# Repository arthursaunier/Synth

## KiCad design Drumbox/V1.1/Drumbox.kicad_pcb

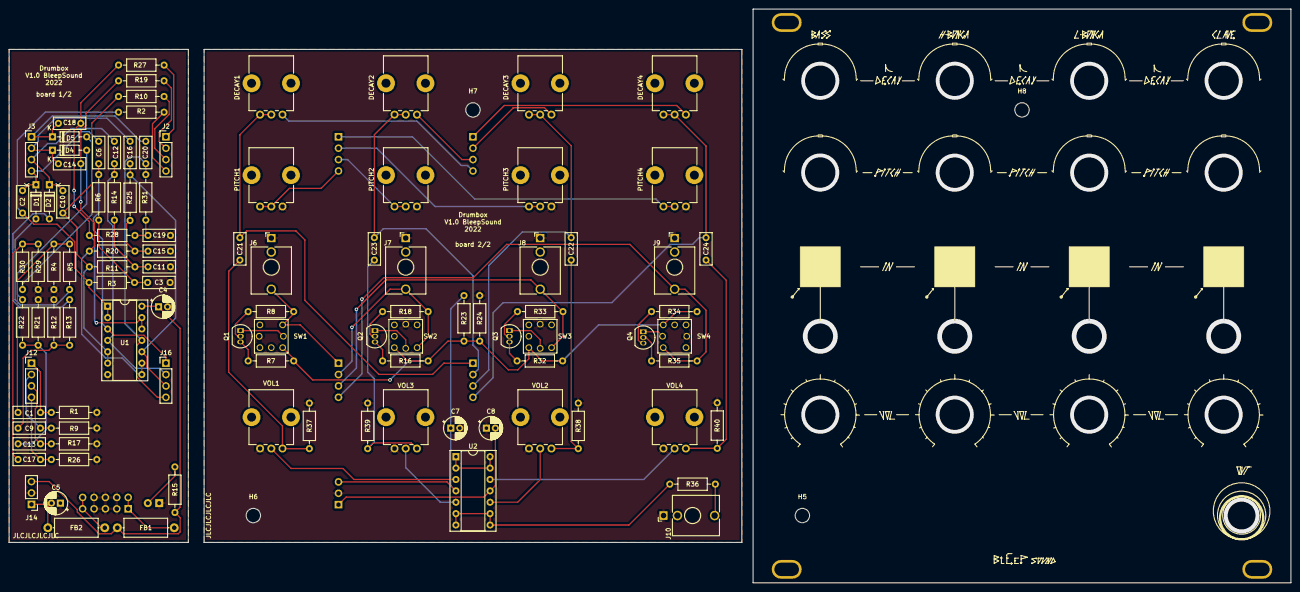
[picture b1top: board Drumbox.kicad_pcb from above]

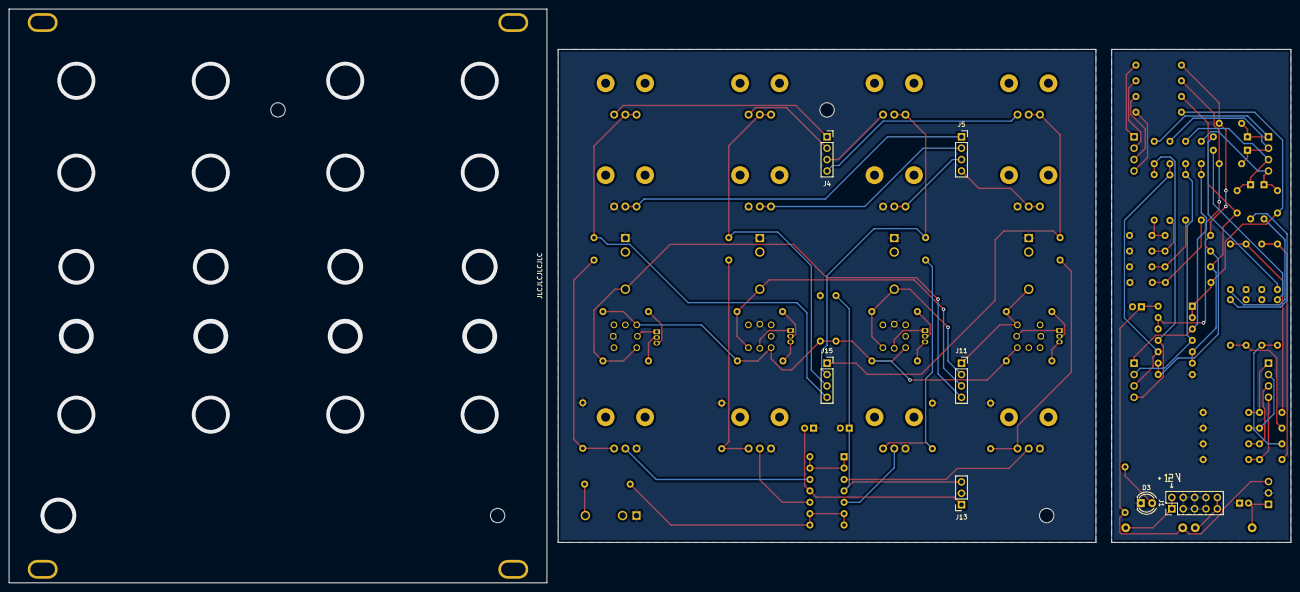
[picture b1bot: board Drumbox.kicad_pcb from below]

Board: 2 copper layers, 286.0 x 128.0 mm, 117 parts (7 on the bottom side), 61 nets.

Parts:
C1, C3: 150nF; C_Disc_D7.0mm_W2.5mm_P5.00mm
C2, C6: 47nF; C_Disc_D7.0mm_W2.5mm_P5.00mm
C4, C5: 10µ; CP_Radial_D5.0mm_P2.00mm
C7, C8: 100n; CP_Radial_D5.0mm_P2.00mm
C9, C11: 33nF; C_Disc_D7.0mm_W2.5mm_P5.00mm
C10, C12: 10nF; C_Disc_D7.0mm_W2.5mm_P5.00mm
C13, C15: 39nF; C_Disc_D7.0mm_W2.5mm_P5.00mm
C14, C16: 12nF; C_Disc_D7.0mm_W2.5mm_P5.00mm
C17: 4.7nF; C_Disc_D7.0mm_W2.5mm_P5.00mm
C18, C20: 1.5nF; C_Disc_D7.0mm_W2.5mm_P5.00mm
C19: 56nF; C_Disc_D7.0mm_W2.5mm_P5.00mm
C21, C22, C23, C24: .1µF; C_Disc_D7.0mm_W2.5mm_P5.00mm
D1, D2, D4, D5: 1N4148; D_DO-35_SOD27_P7.62mm_Horizontal
D3: LED-12V; LED_D4.0mm
DECAY1, DECAY2, DECAY3, DECAY4: 470k; Potentiometer_Bourns_PTV09A-1_Single_Vertical
FB1, FB2: 10R; L_Axial_L9.5mm_D4.0mm_P12.70mm_Horizontal_Fastron_SMCC
H1, H2, H3, H4: MountingHole; Doepfer Mounting hole
H5, H6, H7, H8: SpacerHoles; MountingHole_3.2mm_M3
J1: Power Input; PinHeader_2x05_P2.54mm_Vertical
J2, J3, J12, J16: Conn_01x04_Male; PinHeader_1x04_P2.54mm_Vertical
J4, J5, J11, J15: Conn_01x04_Female; PinSocket_1x04_P2.54mm_Vertical
J6: Bass IN; Jack_3.5mm_QingPu_WQP-PJ398SM_Vertical_CircularHoles
J7: HBonga IN; Jack_3.5mm_QingPu_WQP-PJ398SM_Vertical_CircularHoles
J8: LBonga IN; Jack_3.5mm_QingPu_WQP-PJ398SM_Vertical_CircularHoles
J9: Clave IN; Jack_3.5mm_QingPu_WQP-PJ398SM_Vertical_CircularHoles
J10: Main OUT; Jack_3.5mm_QingPu_WQP-PJ398SM_Vertical_CircularHoles
J13: Conn_01x03_Female; PinSocket_1x03_P2.54mm_Vertical
J14: Conn_01x03_Male; PinHeader_1x03_P2.54mm_Vertical
PITCH1, PITCH2, PITCH3, PITCH4: 10k; Potentiometer_Bourns_PTV09A-1_Single_Vertical
Q1, Q2, Q3, Q4: 2N3904; TO-92_Inline
R1, R9, R17, R26: 12k; R_Axial_DIN0207_L6.3mm_D2.5mm_P10.16mm_Horizontal
R2, R10, R19, R27: 150k; R_Axial_DIN0207_L6.3mm_D2.5mm_P10.16mm_Horizontal
R3, R6, R11, R14, R20, R25, R28, R31: 68k; R_Axial_DIN0207_L6.3mm_D2.5mm_P10.16mm_Horizontal
R4, R12, R21, R23, R29: 47k; R_Axial_DIN0207_L6.3mm_D2.5mm_P10.16mm_Horizontal
R5, R13, R22, R30: 27k; R_Axial_DIN0207_L6.3mm_D2.5mm_P10.16mm_Horizontal
R7, R16, R32, R34, R36: 1k; R_Axial_DIN0207_L6.3mm_D2.5mm_P10.16mm_Horizontal
R8, R18, R33, R35: 100k; R_Axial_DIN0207_L6.3mm_D2.5mm_P10.16mm_Horizontal
R15: 2.2k; R_Axial_DIN0207_L6.3mm_D2.5mm_P10.16mm_Horizontal
R24: 33k; R_Axial_DIN0207_L6.3mm_D2.5mm_P10.16mm_Horizontal
R37, R38, R39, R40: 1M; R_Axial_DIN0207_L6.3mm_D2.5mm_P10.16mm_Horizontal
SW1, SW2, SW3, SW4: SW_MEC_LOW_PROF_LED; PB01-109TL
U1: 4011; DIP-14_W7.62mm_Socket
U2: TL074; DIP-14_W7.62mm_Socket
VOL1, VOL2, VOL3, VOL4: 10k; Potentiometer_Bourns_PTV09A-1_Single_Vertical

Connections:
+5V: R7.1, R16.1, R23.2, R24.1, R32.1, R34.1, SW1.1, SW2.1, SW3.1, SW4.1
+12V: C4.1, C7.1, FB1.1, J13.3, J14.3, R15.1, R23.1, U1.14 (VDD), U2.4 (V+)
-12V: C5.2, C8.2, FB2.1, J13.1, J14.1, U2.11 (V-)
DEIn1: DECAY1.1, J2.4, J4.4, R2.1
DEIn2: DECAY2.1, J2.3, J4.3, R10.1
DEIn3: DECAY3.1, J2.2, J4.2, R19.1
DEIn4: DECAY4.1, J2.1, J4.1, R27.1
GND: C3.2, C4.2, C5.1, C7.2, C8.1, C11.2, C15.2, C19.2, D3.1 (K), J1.3, J1.4, J1.5, J1.6, J1.7, J1.8, J6.S, J7.S, J8.S, J9.S, J10.S, J13.2, J14.2, PITCH1.1, PITCH2.1, PITCH3.1, PITCH4.1, R1.2, R4.1, R9.2, R12.1, R17.2, R21.1, R24.2, R26.2, R29.1, R37.2, R38.2, R39.2, R40.2, SW1.L2, SW2.L2, SW3.L2, SW4.L2, U1.7 (VSS), VOL1.3, VOL2.3, VOL3.3, VOL4.3
In1: C1.1, J6.T, J11.1, J12.1, R1.1, R8.1, SW1.3
In2: C9.1, J7.T, J11.2, J12.2, R9.1, R18.1, SW2.3
In3: C13.1, J8.T, J11.3, J12.3, R17.1, R33.1, SW3.3
In4: C17.1, J9.T, J11.4, J12.4, R26.1, R35.1, SW4.3
unnamed: C1.2, R4.2, R5.1
unnamed: C2.1, R2.2, R3.2, U1.1, U1.2
unnamed: C3.1, R3.1, R6.2
unnamed: C9.2, R12.2, R13.1
unnamed: C10.1, R10.2, R11.2, U1.5, U1.6
unnamed: C11.1, R11.1, R14.2
unnamed: C13.2, R21.2, R22.1
unnamed: C14.1, R19.2, R20.2, U1.8, U1.9
unnamed: C15.1, R20.1, R25.2
unnamed: C17.2, R29.2, R30.1
unnamed: C18.1, R27.2, R28.2, U1.12, U1.13
unnamed: C19.1, R28.1, R31.2
unnamed: C21.2, R37.1, VOL1.1
unnamed: C22.2, R38.1, VOL2.1
unnamed: C23.2, R39.1, VOL3.1
unnamed: C24.2, R40.1, VOL4.1
unnamed: D1.2 (A), R5.2
unnamed: D2.2 (A), R13.2
unnamed: D3.2 (A), R15.2
unnamed: D4.2 (A), R22.2
unnamed: D5.2 (A), R30.2
unnamed: FB1.2, J1.1, J1.2
unnamed: FB2.2, J1.9, J1.10
unnamed: J10.T, R36.1
unnamed: Q1.1 (E), SW1.L1
unnamed: Q1.2 (B), R8.2
unnamed: Q1.3 (C), R7.2
unnamed: Q2.1 (E), SW2.L1
unnamed: Q2.2 (B), R18.2
unnamed: Q2.3 (C), R16.2
unnamed: Q3.1 (E), SW3.L1
unnamed: Q3.2 (B), R33.2
unnamed: Q3.3 (C), R32.2
unnamed: Q4.1 (E), SW4.L1
unnamed: Q4.2 (B), R35.2
unnamed: Q4.3 (C), R34.2
unnamed: U2.3 (+), VOL1.2
unnamed: U2.5 (+), VOL3.2
unnamed: U2.10 (+), VOL2.2
unnamed: U2.12 (+), VOL4.2
O1: C6.2, C21.1, DECAY1.2, DECAY1.3, J15.1, J16.1, R6.1, U1.3
O2: C12.2, C23.1, DECAY2.2, DECAY2.3, J15.2, J16.2, R14.1, U1.4
O3: C16.2, C22.1, DECAY3.2, DECAY3.3, J15.3, J16.3, R25.1, U1.10
O4: C20.2, C24.1, DECAY4.2, DECAY4.3, J15.4, J16.4, R31.1, U1.11
Out1: R36.2, U2.1, U2.2 (-), U2.6 (-), U2.7, U2.8, U2.9 (-), U2.13 (-), U2.14
PIOut1: C2.2, C6.1, D1.1 (K), J3.4, J5.4, PITCH1.2, PITCH1.3
PIOut2: C10.2, C12.1, D2.1 (K), J3.3, J5.3, PITCH2.2, PITCH2.3
PIOut3: C14.2, C16.1, D4.1 (K), J3.2, J5.2, PITCH3.2, PITCH3.3
PIOut4: C18.2, C20.1, D5.1 (K), J3.1, J5.1, PITCH4.2, PITCH4.3

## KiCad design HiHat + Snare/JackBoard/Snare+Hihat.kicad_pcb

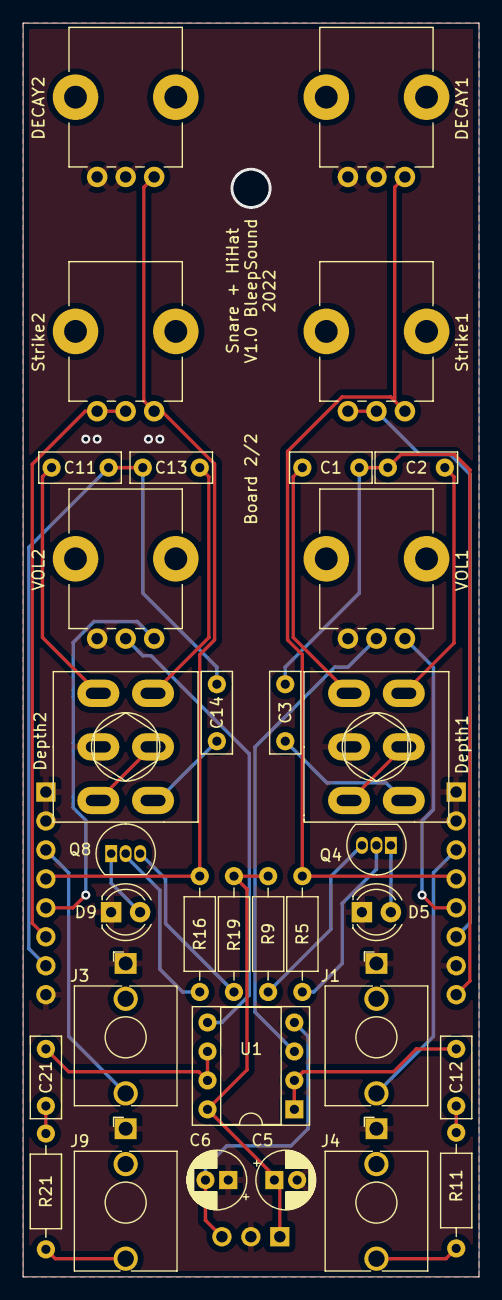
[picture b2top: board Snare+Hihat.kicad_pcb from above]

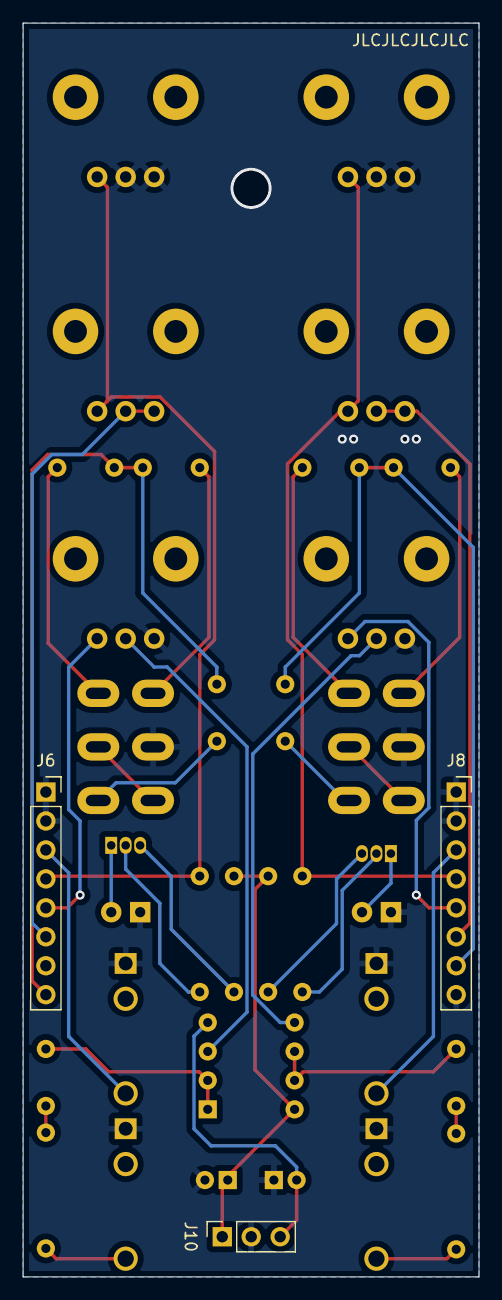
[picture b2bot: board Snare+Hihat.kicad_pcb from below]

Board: 2 copper layers, 40.0 x 110.0 mm, 36 parts (3 on the bottom side), 35 nets.

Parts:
C1, C11, C12, C21: 10µF; C_Disc_D7.0mm_W2.5mm_P5.00mm
C2, C13: 1µF; C_Disc_D7.0mm_W2.5mm_P5.00mm
C3, C14: 0.1µF; C_Disc_D7.0mm_W2.5mm_P5.00mm
C5, C6: 10µ; CP_Radial_D5.0mm_P2.00mm
D5: Trig Snare; LED_D4.0mm
D9: Trig_HiHat; LED_D4.0mm
DECAY1, DECAY2: 100k; Potentiometer_Bourns_PTV09A-1_Single_Vertical
Depth1, Depth2: SW_Push_DPDT; SW_DPDT_Toggle
J1: Snare IN; Jack_3.5mm_QingPu_WQP-PJ398SM_Vertical_CircularHoles
J3: HiHat IN; Jack_3.5mm_QingPu_WQP-PJ398SM_Vertical_CircularHoles
J4: Snare OUT; Jack_3.5mm_QingPu_WQP-PJ398SM_Vertical_CircularHoles
J6, J8: Conn_01x08_Female; PinSocket_1x08_P2.54mm_Vertical
J9: HiHat OUT; Jack_3.5mm_QingPu_WQP-PJ398SM_Vertical_CircularHoles
J10: Conn_01x03_Female; PinSocket_1x03_P2.54mm_Vertical
Q4, Q8: 2N3904; TO-92_Inline
R5, R16: 100k; R_Axial_DIN0207_L6.3mm_D2.5mm_P10.16mm_Horizontal
R9, R11, R19, R21: 1k; R_Axial_DIN0207_L6.3mm_D2.5mm_P10.16mm_Horizontal
Strike1, Strike2: 100k; Potentiometer_Bourns_PTV09A-1_Single_Vertical
U1: TL072; DIP-8_W7.62mm_Socket
VOL1, VOL2: 10k; Potentiometer_Bourns_PTV09A-1_Single_Vertical

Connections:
+12V: C5.1, J10.1, R9.1, R19.1, U1.8 (V+)
-12V: C6.2, J10.3, U1.4 (V-)
/DeH: C1.1, C2.1, C3.1, J6.8
/HiDH: C11.1, C13.1, C14.1, J8.7
/HiH: DECAY2.1, J8.4, R16.1, Strike2.1
/HiI: J3.T, J8.3
/HiO: J8.5, VOL2.1
/Ho: J8.6, Strike2.2, Strike2.3
/SnH: DECAY1.1, J6.4, R5.1, Strike1.1
/SnI: J1.T, J6.3
/SnO: J6.5, VOL1.1
/So: J6.6, Strike1.2, Strike1.3
GND: C5.2, C6.1, D5.1 (K), D9.1 (K), DECAY1.2, DECAY1.3, DECAY2.2, DECAY2.3, Depth1.2 (B), Depth2.2 (B), J1.S, J3.S, J4.S, J6.1, J6.2, J6.7, J8.1, J8.2, J8.8, J9.S, J10.2, VOL1.3, VOL2.3
unnamed: C1.2, Depth1.1 (A)
unnamed: C2.2, Depth1.4 (A)
unnamed: C3.2, Depth1.6 (C)
unnamed: C11.2, Depth2.1 (A)
unnamed: C12.2, R11.2
unnamed: C13.2, Depth2.4 (A)
unnamed: C14.2, Depth2.6 (C)
unnamed: C21.1, U1.6 (-), U1.7
unnamed: C21.2, R21.2
unnamed: D5.2 (A), Q4.1 (E)
unnamed: D9.2 (A), Q8.1 (E)
unnamed: Depth1.3 (C), Depth1.5 (B)
unnamed: Depth2.3 (C), Depth2.5 (B)
unnamed: Q4.2 (B), R5.2
unnamed: Q4.3 (C), R9.2
unnamed: Q8.2 (B), R16.2
unnamed: Q8.3 (C), R19.2
unnamed: J4.T, R11.1
unnamed: J9.T, R21.1
unnamed: C12.1, U1.1, U1.2 (-)
unnamed: U1.3 (+), VOL1.2
unnamed: U1.5 (+), VOL2.2
